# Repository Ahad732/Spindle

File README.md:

# Spindle

Spindle is a low-cost, custom e-reader made with the RP2350A. It consists of a 2.7 inch e-paper display, which is much better than a typical screen. It also consists of a 128Mbit flash, which is 16MiB, and 5 user buttons. The firmware for Spindle can be found [here](https://github.com/Keyaan-07/spindle-firmware/tree/main). The firmware is custom written in C. The power consumption averages at about 40mA, making it a low-power device.  

See the board on [KiCanvas](https://kicanvas.org/?repo=https%3A%2F%2Fgithub.com%2FAhad732%2FSpindle%2Ftree%2Fmain%2FHardware)  

## Features:
- Dual ARM-Cortex M-33 and Hazard3 RISC-V cores
- WiFi Functionality
- 16MiB flash
- 2.7 inch e-paper display
- 100% open-sourced
- USB High Speed compatible
- switching charging
- low-power consumption

# CAD: 
So, the CAD is made in onshape, [link here](https://cad.onshape.com/documents/20ea073a3a4d1e1a3f911dd9/w/66e638eb5b2ab30e1451aaff/e/b663f709698147c3db960dcd). We have tried our best to make it look as clean as possible.  This is what the assembly looks like:  

## Images:  

We made this project as a fun way to learn to integrate various components and work together on different parts of the same project!  

# BOM
|Designator                                      |Footprint                                        |Value                      |Quantity            |Price|Link                                                                                 |
|------------------------------------------------|-------------------------------------------------|---------------------------|--------------------|-----|-------------------------------------------------------------------------------------|
|C1, C2                                          |402                                              |15p                        |100                 |0.09 |https://www.lcsc.com/product-detail/C696887.html                                     |
|C10, C11, C12, C4, C6, C7, C8, C9               |402                                              |1u                         |100                 |0.58 |https://www.lcsc.com/product-detail/C46614477.html                                   |
|C13, C14, C15, C16, C17, C18, C19, C20, C21, C24|402                                              |100n                       |100                 |0.16 |https://www.lcsc.com/product-detail/C5137487.html                                    |
|C23, C25, C26, C27, C3, C5                      |402                                              |4.7u                       |20                  |0.42 |https://www.lcsc.com/product-detail/C318563.html                                     |
|D1                                              |402                                              |GREEN                      |100                 |0.61 |https://www.lcsc.com/product-detail/C55072283.html                                   |
|D2                                              |402                                              |RED                        |100                 |0.55 |https://www.lcsc.com/product-detail/C55072282.html                                   |
|D3, D4, D5                                      |D_SOD-123                                        |MBR0530                    |20                  |0.74 |https://www.lcsc.com/product-detail/C5140024.html                                    |
|J1                                              |USB_C_Receptacle_HCTL_HC-TYPE-C-16P-01A          |USB_C_Receptacle_USB2.0_16P|20                  |0.48 |https://www.lcsc.com/product-detail/C42400234.html                                   |
|J2                                              |PinHeader_1x02_P2.54mm_Vertical                  |Conn_01x02_Pin             |DNP                 |DNP  |                                                                                     |
|J3                                              |Hirose_FH12-24S-0.5SH_1x24-1MP_P0.50mm_Horizontal|Conn_01x24_Pin             |10                  |0.67 |https://www.lcsc.com/product-detail/C19273933.html                                   |
|J4                                              |microSD_HC_Molex_104031-0811                     |Micro_SD_Card              |3                   |2.5  |https://www.lcsc.com/product-detail/C585350.html                                     |
|L1                                              |L_Radial_D6.0mm_P4.00mm                          |47u                        |5                   |0.53 |https://www.lcsc.com/product-detail/C72618.html                                      |
|L2                                              |L_Sunlord_SWPA5040S                              |3.3u                       |20                  |0.77 |https://www.lcsc.com/product-detail/C5289414.html                                    |
|Q1                                              |SOT-323_SC-70                                    |Si1308EDL                  |5                   |0.59 |https://www.lcsc.com/product-detail/C4355112.html                                    |
|R1                                              |402                                              |60.4K                      |100                 |0.09 |https://www.lcsc.com/product-detail/C49653007.html                                   |
|R10                                             |402                                              |1M                         |100                 |0.08 |https://www.lcsc.com/product-detail/C49652954.html                                   |
|R11, R12, R13, R14, R15, R16, R17, R2           |402                                              |10K                        |100                 |0.11 |https://www.lcsc.com/product-detail/C49653007.html                                   |
|R18                                             |402                                              |470                        |100                 |0.06 |https://www.lcsc.com/product-detail/C54920802.html                                   |
|R3, R4, R7                                      |402                                              |1.5K                       |100                 |0.06 |https://www.lcsc.com/product-detail/C54920744.html                                   |
|R5, R6                                          |402                                              |5.1K                       |100                 |0.06 |https://www.lcsc.com/product-detail/C54920813.html                                   |
|R8                                              |402                                              |1K                         |100                 |0.07 |https://www.lcsc.com/product-detail/C54920633.html                                   |
|R9                                              |402                                              |2.2                        |100                 |0.07 |https://www.lcsc.com/product-detail/C54920775.html                                   |
|SW1, SW2, SW3, SW4, SW5, SW6                    |SW_SPST_PTS810                                   |SW_Push                    |10                  |3.43 |https://www.lcsc.com/product-detail/C221895.html                                     |
|U1                                              |QFN-60-1EP_7x7mm_P0.4mm_EP3.4x3.4mm              |RP2350A                    |3                   |3.9  |https://www.lcsc.com/product-detail/C42411118.html                                   |
|U2                                              |VQFN-16-1EP_3x3mm_P0.5mm_EP1.6x1.6mm             |BQ24074RGT                 |3                   |7.59 |https://www.lcsc.com/product-detail/C54313.html                                      |
|U3                                              |SOT-23                                           |MCP1700x-330xxTT           |5                   |0.59 |https://www.lcsc.com/product-detail/C41381676.html                                   |
|U4                                              |WSON-8-1EP_6x5mm_P1.27mm_EP3.4x4.3mm             |W25Q128JVP                 |3                   |2.32 |https://www.lcsc.com/product-detail/C2641199.html                                    |
|U5                                              |rpi_rmc20452t                                    |rpi_rmc20452t              |2                   |10.33|https://www.lioncircuits.com/parts/SC1169                                            |
|Y1                                              |Crystal_SMD_3225-4Pin_3.2x2.5mm                  |12mhz                      |10                  |0.55 |https://www.lcsc.com/product-detail/C16197268.html                                   |
|                                                |                                                 |Battery                    |1                   |4.87 |https://robu.in/product/wly103443-1500mah-3-7v-single-cell-rechargeable-lipo-battery/|
|                                                |                                                 |Screen                     |1                   |14.52|https://robu.in/product/2-7-inch-black-white-e-paper-good-display-with-touch-panel/  |
|                                                |                                                 |                           |PCB+Stencil+Shipping|22.35|                                                                                     |
|                                                |                                                 |                           |Parts Shipping      |8.82 |                                                                                     |
|                                                |                                                 |                           |Total               |88.56|                                                                                     |

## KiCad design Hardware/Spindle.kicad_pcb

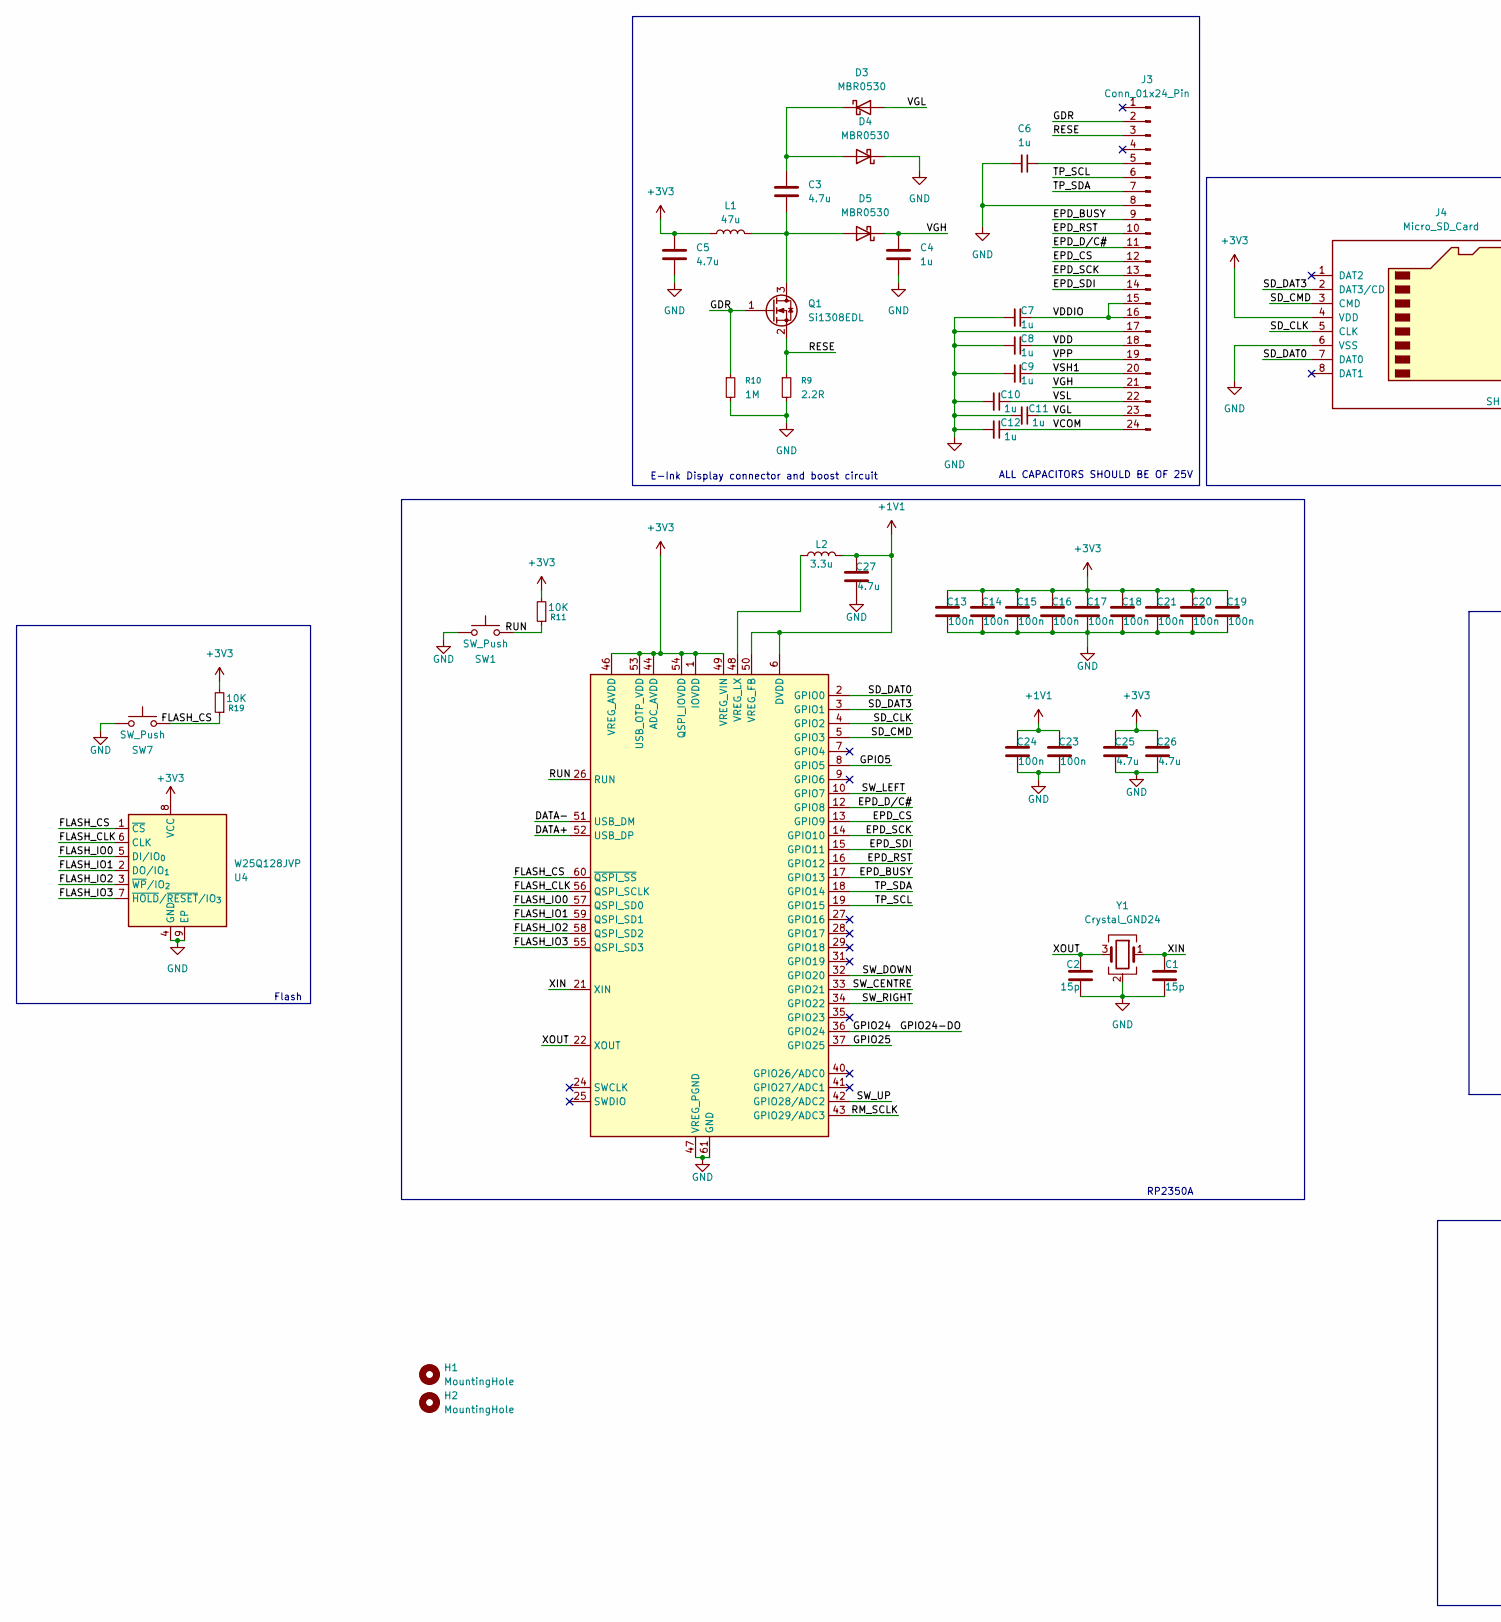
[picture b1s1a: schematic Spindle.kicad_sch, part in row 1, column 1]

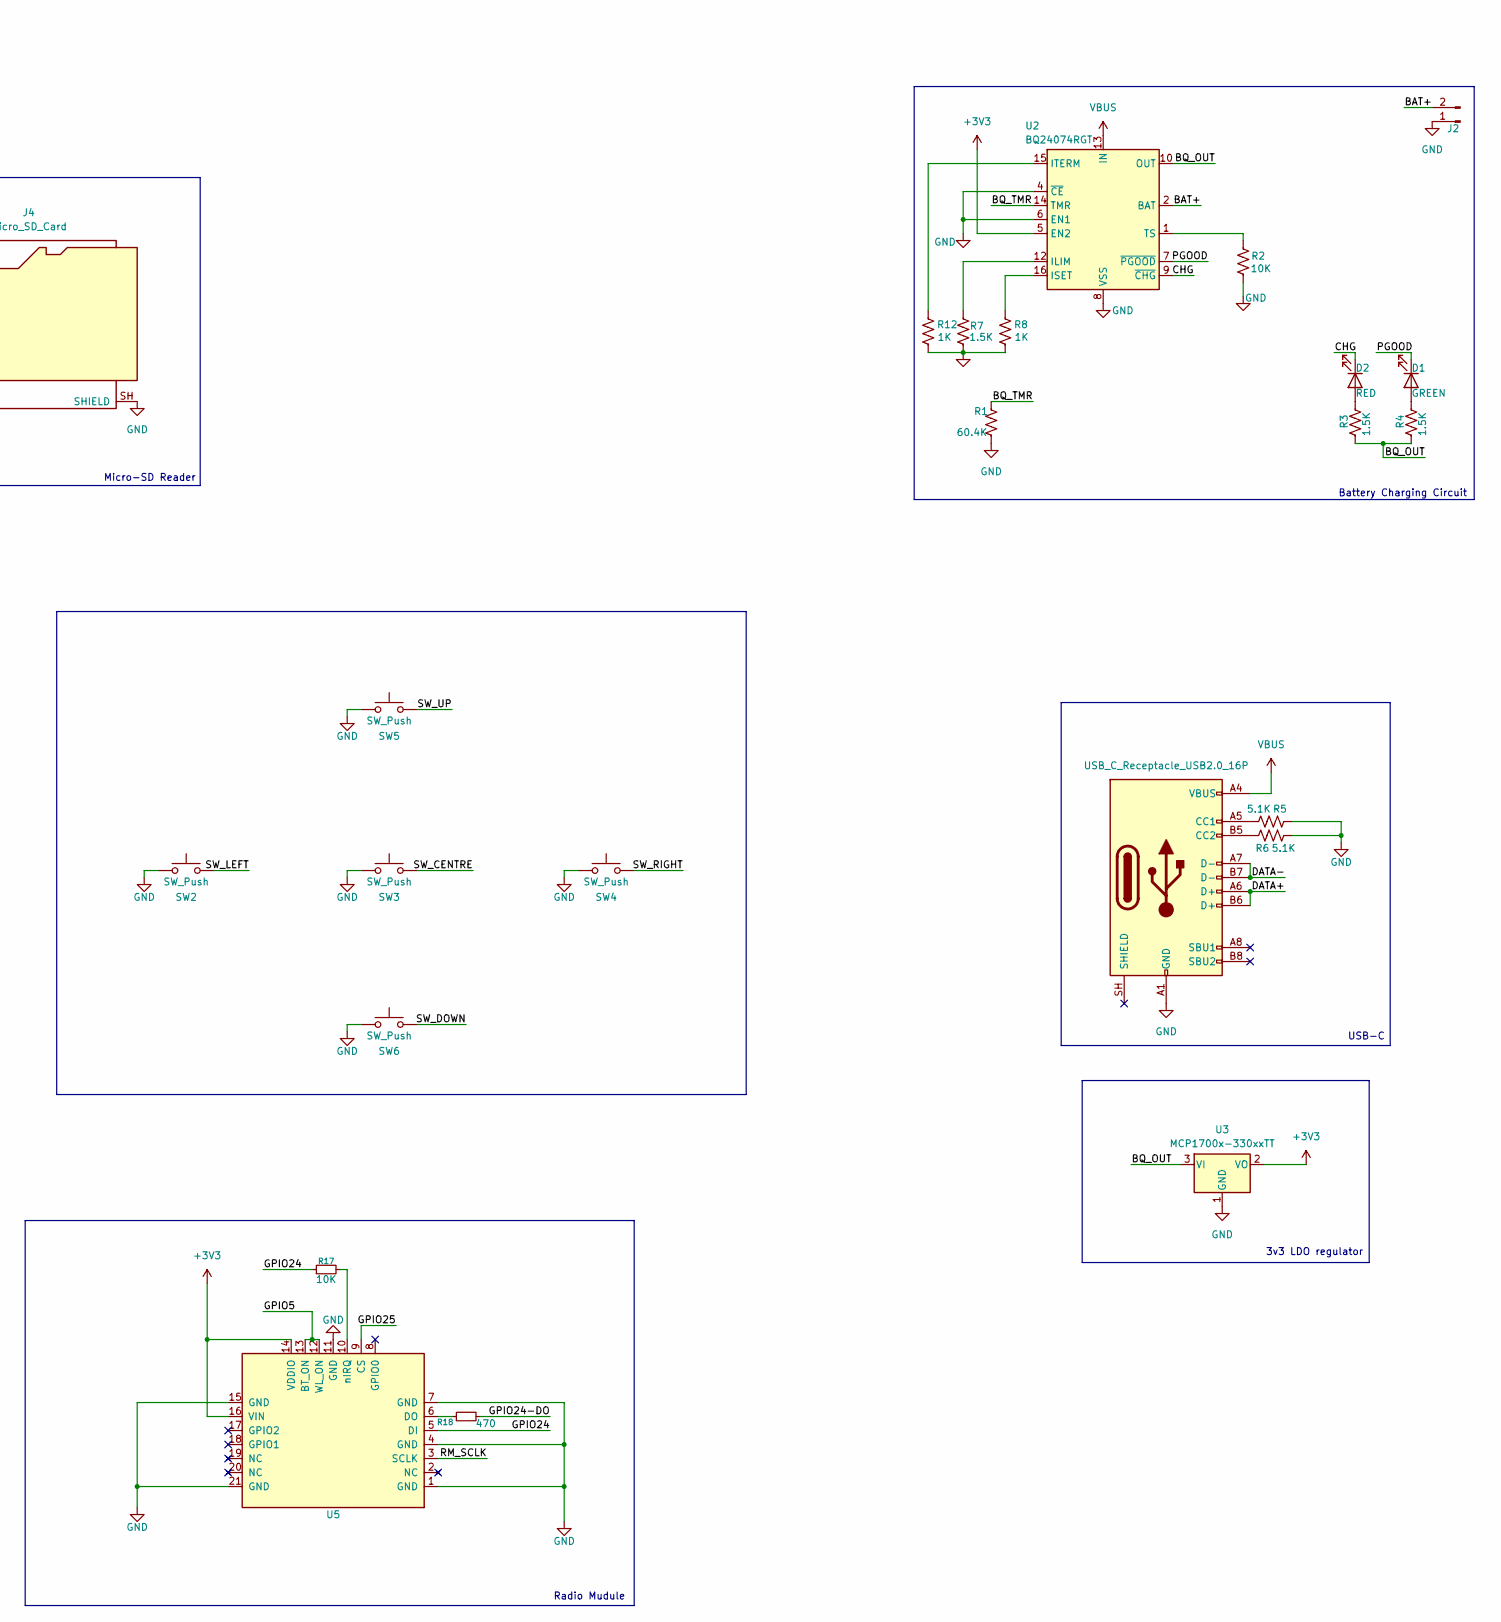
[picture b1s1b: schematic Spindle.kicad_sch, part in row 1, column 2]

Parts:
C1, C2: 15p; C_0402_1005Metric
C3, C5, C25, C26, C27: 4.7u; C_0402_1005Metric
C4, C6, C7, C8, C9, C10, C11, C12: 1u; C_0402_1005Metric
C13, C14, C15, C16, C17, C18, C19, C20, C21, C23, C24: 100n; C_0402_1005Metric
D1: GREEN; LED_0402_1005Metric
D2: RED; LED_0402_1005Metric
D3, D4, D5: MBR0530; D_SOD-123
H1, H2: MountingHole; MountingHole_3.2mm_M3
J1: USB_C_Receptacle_USB2.0_16P; USB_C_Receptacle_HCTL_HC-TYPE-C-16P-01A
J2: Conn_01x02_Pin; PinHeader_1x02_P2.54mm_Vertical
J3: Conn_01x24_Pin; Hirose_FH12-24S-0.5SH_1x24-1MP_P0.50mm_Horizontal
J4: Micro_SD_Card; microSD_HC_Molex_104031-0811
L1: 47u; L_Sunlord_SWPA5040S
L2: 3.3u; IND-SMD_L2.0-W1.6_AOTA-B201610S3R3-101-T
Q1: Si1308EDL; SOT-323_SC-70
R1: 60.4K; R_0402_1005Metric
R2, R11, R17, R19: 10K; R_0402_1005Metric
R3, R4, R7: 1.5K; R_0402_1005Metric
R5, R6: 5.1K; R_0402_1005Metric
R8, R12: 1K; R_0402_1005Metric
R9: 2.2R; R_0402_1005Metric
R10: 1M; R_0402_1005Metric
R18: 470; R_0402_1005Metric
SW1, SW2, SW3, SW4, SW5, SW6, SW7: SW_Push; SW_SPST_PTS810
U1: RP2350A; QFN-60-1EP_7x7mm_P0.4mm_EP3.4x3.4mm
U2: BQ24074RGT; VQFN-16-1EP_3x3mm_P0.5mm_EP1.6x1.6mm
U3: MCP1700x-330xxTT; SOT-23
U4: W25Q128JVP; WSON-8-1EP_6x5mm_P1.27mm_EP3.4x4.3mm
U5: <value>; rpi_rmc20452t
Y1: Crystal_GND24; Crystal_SMD_3225-4Pin_3.2x2.5mm

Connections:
+1V1: C23.1, C24.1, C27.1, L2.2, U1.6 (DVDD), U1.23 (DVDD), U1.39 (DVDD), U1.50 (VREG_FB)
+3V3: C5.1, C13.1, C14.1, C15.1, C16.1, C17.1, C18.1, C19.1, C20.1, C21.1, C25.1, C26.1, J4.4 (VDD), L1.1, R11.2, R19.2, U1.1 (IOVDD), U1.11 (IOVDD), U1.20 (IOVDD), U1.30 (IOVDD), U1.38 (IOVDD), U1.44 (ADC_AVDD), U1.45 (IOVDD), U1.46 (VREG_AVDD), U1.49 (VREG_VIN), U1.53 (USB_OTP_VDD), U1.54 (QSPI_IOVDD), U2.5 (EN2), U3.2 (VO), U4.8 (VCC), U5.14 (VDDIO), U5.16 (VIN)
/BAT+: J2.2, U2.2 (BAT), U2.3 (BAT)
/BQ_OUT: R3.2, R4.2, U2.10 (OUT), U2.11 (OUT), U3.3 (VI)
/BQ_TMR: R1.1, U2.14 (TMR)
/CHG: D2.1 (K), U2.9 (~CHG)
/DATA+: J1.A6 (D+), J1.B6 (D+), U1.52 (USB_DP)
/DATA-: J1.A7 (D-), J1.B7 (D-), U1.51 (USB_DM)
/EPD_BUSY: J3.9, U1.17 (GPIO13)
/EPD_CS: J3.12, U1.13 (GPIO9)
/EPD_D/C#: J3.11, U1.12 (GPIO8)
/EPD_RST: J3.10, U1.16 (GPIO12)
/EPD_SCK: J3.13, U1.14 (GPIO10)
/EPD_SDI: J3.14, U1.15 (GPIO11)
/FLASH_CLK: U1.56 (QSPI_SCLK), U4.6 (CLK)
/FLASH_CS: R19.1, SW7.2, U1.60 (~QSPI_SS), U4.1 (~CS)
/FLASH_IO0: U1.57 (QSPI_SD0), U4.5 (DI/IO_{0})
/FLASH_IO1: U1.59 (QSPI_SD1), U4.2 (DO/IO_{1})
/FLASH_IO2: U1.58 (QSPI_SD2), U4.3 (~WP/IO_{2})
/FLASH_IO3: U1.55 (QSPI_SD3), U4.7 (~HOLD/~RESET/IO_{3})
/GDR: J3.2, Q1.1 (G), R10.1
/GPIO5: U1.8 (GPIO5), U5.12 (WL_ON), U5.13 (BT_ON)
/GPIO24: R17.1, R18.2, U1.36 (GPIO24), U5.5 (DI)
/GPIO25: U1.37 (GPIO25), U5.9 (CS)
/PGOOD: D1.1 (K), U2.7 (~PGOOD)
/RESE: J3.3, Q1.2 (S), R9.1
/RM_SCLK: U1.43 (GPIO29/ADC3), U5.3 (SCLK)
/RUN: R11.1, SW1.2, U1.26 (RUN)
/SD_CLK: J4.5 (CLK), U1.4 (GPIO2)
/SD_CMD: J4.3 (CMD), U1.5 (GPIO3)
/SD_DAT0: J4.7 (DAT0), U1.2 (GPIO0)
/SD_DAT3: J4.2 (DAT3/CD), U1.3 (GPIO1)
/SW_CENTRE: SW3.2, U1.33 (GPIO21)
/SW_DOWN: SW6.2, U1.32 (GPIO20)
/SW_LEFT: SW2.2, U1.10 (GPIO7)
/SW_RIGHT: SW4.2, U1.34 (GPIO22)
/SW_UP: SW5.2, U1.42 (GPIO28/ADC2)
/TP_SCL: J3.6, U1.19 (GPIO15)
/TP_SDA: J3.7, U1.18 (GPIO14)
/VCOM: C12.1, J3.24
/VDD: C8.1, J3.18
/VDDIO: C7.1, J3.15, J3.16
/VGH: C4.1, D5.1 (K), J3.21
/VGL: C11.1, D3.2 (A), J3.23
/VPP: J3.19
/VSH1: C9.1, J3.20
/VSL: C10.1, J3.22
/XIN: C1.2, U1.21 (XIN), Y1.1
/XOUT: C2.1, U1.22 (XOUT), Y1.3
GND: C1.1, C2.2, C4.2, C5.2, C6.2, C7.2, C8.2, C9.2, C10.2, C11.2, C12.2, C13.2, C14.2, C15.2, C16.2, C17.2, C18.2, C19.2, C20.2, C21.2, C23.2, C24.2, C25.2, C26.2, C27.2, D4.1 (K), J1.A1 (GND), J1.A12 (GND), J1.B1 (GND), J1.B12 (GND), J2.1, J3.8, J3.17, J4.6 (VSS), J4.SH (SHIELD), R1.2, R2.1, R5.2, R6.1, R7.1, R8.2, R9.2, R10.2, R12.2, SW1.1, SW2.1, SW3.1, SW4.1, SW5.1, SW6.1, SW7.1, U1.47 (VREG_PGND), U1.61 (GND), U2.4 (~CE), U2.6 (EN1), U2.8 (VSS), U2.17 (VSS), U3.1 (GND), U4.4 (GND), U4.9 (EP), U5.1 (GND), U5.4 (GND), U5.7 (GND), U5.11 (GND), U5.15 (GND), U5.21 (GND), Y1.2 (G), Y1.4 (G)
unnamed: D1.2 (A), R4.1
unnamed: D2.2 (A), R3.1
unnamed: C3.1, D3.1 (K), D4.2 (A)
unnamed: C3.2, D5.2 (A), L1.2, Q1.3 (D)
unnamed: J1.A5 (CC1), R5.1
unnamed: J1.B5 (CC2), R6.2
unnamed: C6.1, J3.5
unnamed: R12.1, U2.15 (ITERM)
unnamed: L2.1, U1.48 (VREG_LX)
unnamed: R7.2, U2.12 (ILIM)
unnamed: R8.1, U2.16 (ISET)
unnamed: R2.2, U2.1 (TS)
unnamed: R18.1, U5.6 (DO)
unnamed: R17.2, U5.10 (nIRQ)
VBUS: J1.A4 (VBUS), J1.A9 (VBUS), J1.B4 (VBUS), J1.B9 (VBUS), U2.13 (IN)

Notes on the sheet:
Battery Charging Circuit
E-Ink Display connector and boost circuit
Radio Mudule
Flash
Micro-SD Reader
RP2350A
3v3 LDO regulator
USB-C
ALL CAPACITORS SHOULD BE OF 25V

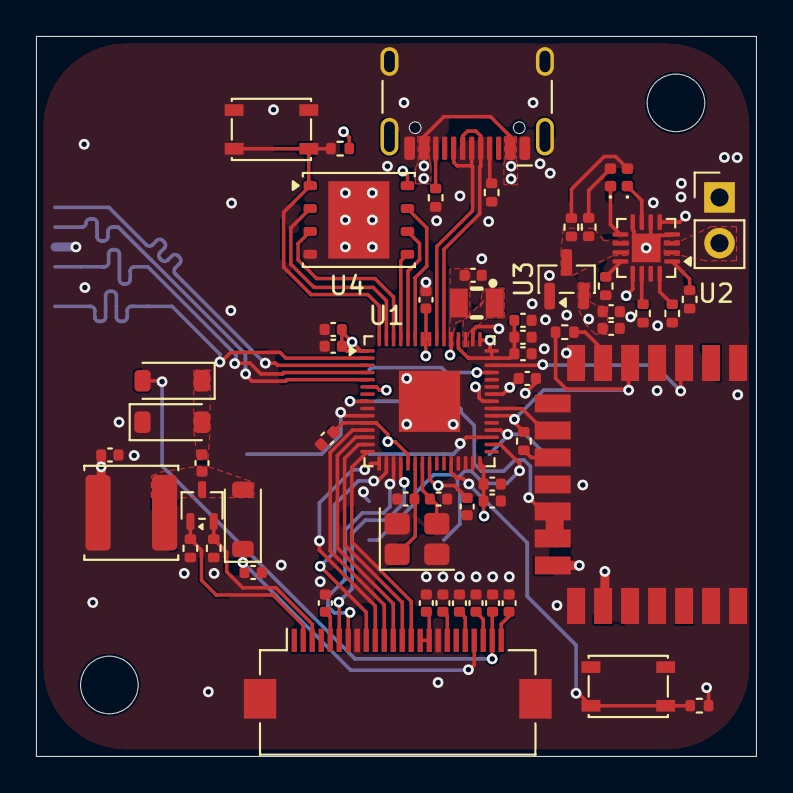
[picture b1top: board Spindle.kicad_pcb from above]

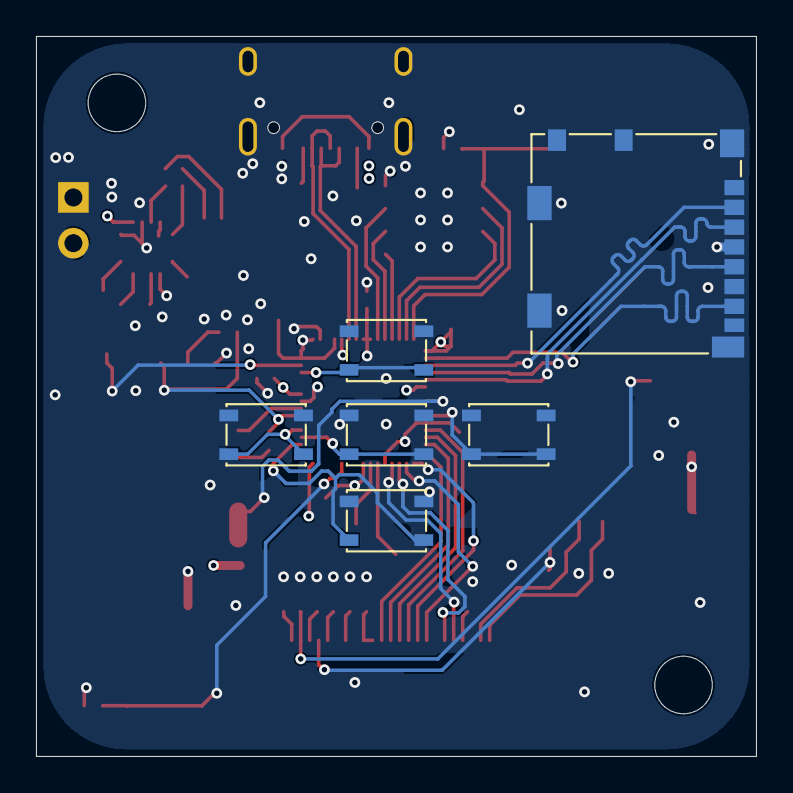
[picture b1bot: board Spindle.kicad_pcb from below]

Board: 4 copper layers, 40.0 x 40.0 mm, 67 parts (6 on the bottom side), 63 nets.

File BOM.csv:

Designator,Footprint,Value,Quantity,Price,Link
"C1, C2",402,15p,100,0.09,https://www.lcsc.com/product-detail/C696887.html
"C10, C11, C12, C4, C6, C7, C8, C9",402,1u,100,0.58,https://www.lcsc.com/product-detail/C46614477.html
"C13, C14, C15, C16, C17, C18, C19, C20, C21, C24",402,100n,100,0.16,https://www.lcsc.com/product-detail/C5137487.html
"C23, C25, C26, C27, C3, C5",402,4.7u,20,0.42,https://www.lcsc.com/product-detail/C318563.html
D1,402,GREEN,100,0.61,https://www.lcsc.com/product-detail/C55072283.html
D2,402,RED,100,0.55,https://www.lcsc.com/product-detail/C55072282.html
"D3, D4, D5",D_SOD-123,MBR0530,20,0.74,https://www.lcsc.com/product-detail/C5140024.html
J1,USB_C_Receptacle_HCTL_HC-TYPE-C-16P-01A,USB_C_Receptacle_USB2.0_16P,20,0.48,https://www.lcsc.com/product-detail/C42400234.html
J2,PinHeader_1x02_P2.54mm_Vertical,Conn_01x02_Pin,DNP,DNP,
J3,Hirose_FH12-24S-0.5SH_1x24-1MP_P0.50mm_Horizontal,Conn_01x24_Pin,10,0.67,https://www.lcsc.com/product-detail/C19273933.html
J4,microSD_HC_Molex_104031-0811,Micro_SD_Card,3,2.5,https://www.lcsc.com/product-detail/C585350.html
L1,L_Radial_D6.0mm_P4.00mm,47u,5,0.53,https://www.lcsc.com/product-detail/C72618.html
L2,L_Sunlord_SWPA5040S,3.3u,20,0.77,https://www.lcsc.com/product-detail/C5289414.html
Q1,SOT-323_SC-70,Si1308EDL,5,0.59,https://www.lcsc.com/product-detail/C4355112.html
R1,402,60.4K,100,0.09,https://www.lcsc.com/product-detail/C49653007.html
R10,402,1M,100,0.08,https://www.lcsc.com/product-detail/C49652954.html
"R11, R12, R13, R14, R15, R16, R17, R2",402,10K,100,0.11,https://www.lcsc.com/product-detail/C49653007.html
R18,402,470,100,0.06,https://www.lcsc.com/product-detail/C54920802.html
"R3, R4, R7",402,1.5K,100,0.06,https://www.lcsc.com/product-detail/C54920744.html
"R5, R6",402,5.1K,100,0.06,https://www.lcsc.com/product-detail/C54920813.html
R8,402,1K,100,0.07,https://www.lcsc.com/product-detail/C54920633.html
R9,402,2.2,100,0.07,https://www.lcsc.com/product-detail/C54920775.html
"SW1, SW2, SW3, SW4, SW5, SW6",SW_SPST_PTS810,SW_Push,10,3.43,https://www.lcsc.com/product-detail/C221895.html
U1,QFN-60-1EP_7x7mm_P0.4mm_EP3.4x3.4mm,RP2350A,3,3.9,https://www.lcsc.com/product-detail/C42411118.html
U2,VQFN-16-1EP_3x3mm_P0.5mm_EP1.6x1.6mm,BQ24074RGT,3,7.59,https://www.lcsc.com/product-detail/C54313.html
U3,SOT-23,MCP1700x-330xxTT,5,0.59,https://www.lcsc.com/product-detail/C41381676.html
U4,WSON-8-1EP_6x5mm_P1.27mm_EP3.4x4.3mm,W25Q128JVP,3,2.32,https://www.lcsc.com/product-detail/C2641199.html
U5,rpi_rmc20452t,rpi_rmc20452t,2,10.33,https://www.lioncircuits.com/parts/SC1169
Y1,Crystal_SMD_3225-4Pin_3.2x2.5mm,12mhz,10,0.55,https://www.lcsc.com/product-detail/C16197268.html
,,Battery,1,4.87,https://robu.in/product/wly103443-1500mah-3-7v-single-cell-r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
,,Screen,1,14.52,https://robu.in/product/2-7-inch-black-white-e-paper-good-di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
,,,PCB+Stencil+Shipping,22.35,
,,,Parts Shipping,8.82,
,,,Total,88.56,
